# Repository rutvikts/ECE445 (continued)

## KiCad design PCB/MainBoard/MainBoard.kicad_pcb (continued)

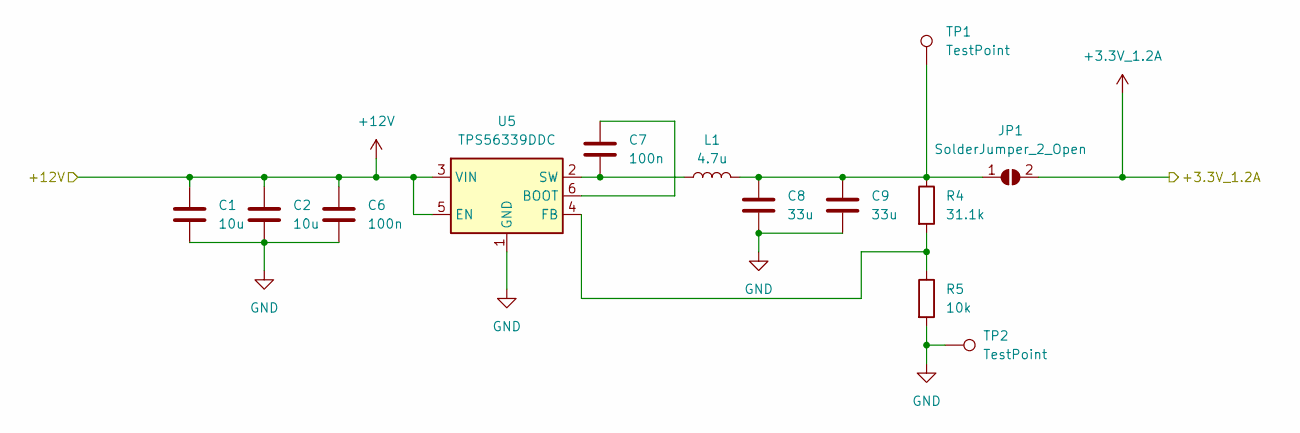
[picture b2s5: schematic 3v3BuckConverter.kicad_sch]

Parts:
C1, C2: 10u; C_1206_3216Metric_Pad1.33x1.80mm_HandSolder
C6, C7: 100n; C_1206_3216Metric_Pad1.33x1.80mm_HandSolder
C8, C9: 33u; C_1206_3216Metric_Pad1.33x1.80mm_HandSolder
JP1: SolderJumper_2_Open; SolderJumper-2_P1.3mm_Open_TrianglePad1.0x1.5mm
L1: 4.7u; L_1008_2520Metric
R4: 31.1k; R_Axial_DIN0207_L6.3mm_D2.5mm_P7.62mm_Horizontal
R5: 10k; R_Axial_DIN0207_L6.3mm_D2.5mm_P7.62mm_Horizontal
TP1, TP2: TestPoint; PinHeader_1x01_P2.54mm_Vertical
U5: TPS56339DDC; SOT-23-6

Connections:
+3.3V_1.2A: JP1.2 (B); also elsewhere on the board
+12V: C1.1, C2.1, C6.1, U5.3 (VIN), U5.5 (EN); also elsewhere on the board
GND: C1.2, C2.2, C6.2, C8.2, C9.2, R5.2, TP2.1, U5.1 (GND); also elsewhere on the board
unnamed: C8.1, C9.1, JP1.1 (A), L1.2, R4.1, TP1.1
unnamed: C7.1, U5.6 (BOOT)
unnamed: R4.2, R5.1, U5.4 (FB)
unnamed: C7.2, L1.1, U5.2 (SW)

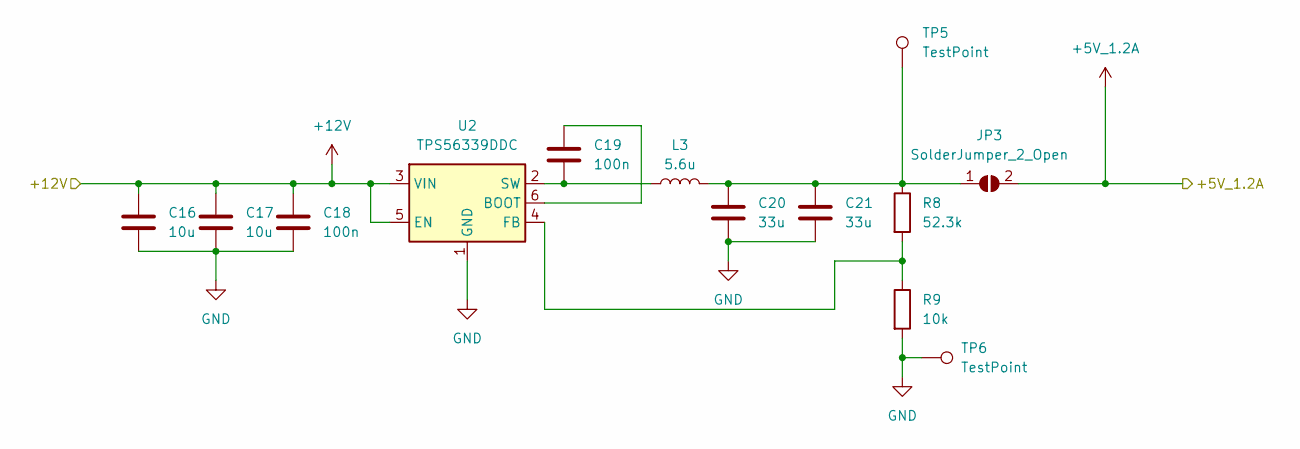
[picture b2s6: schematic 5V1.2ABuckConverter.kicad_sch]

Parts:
C16, C17: 10u; C_1206_3216Metric_Pad1.33x1.80mm_HandSolder
C18, C19: 100n; C_1206_3216Metric_Pad1.33x1.80mm_HandSolder
C20, C21: 33u; C_1206_3216Metric_Pad1.33x1.80mm_HandSolder
JP3: SolderJumper_2_Open; SolderJumper-2_P1.3mm_Open_TrianglePad1.0x1.5mm
L3: 5.6u; L_1008_2520Metric
R8: 52.3k; R_Axial_DIN0207_L6.3mm_D2.5mm_P7.62mm_Horizontal
R9: 10k; R_Axial_DIN0207_L6.3mm_D2.5mm_P7.62mm_Horizontal
TP5, TP6: TestPoint; PinHeader_1x01_P2.54mm_Vertical
U2: TPS56339DDC; SOT-23-6

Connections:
+5V_1.2A: JP3.2 (B); also elsewhere on the board
+12V: C16.1, C17.1, C18.1, U2.3 (VIN), U2.5 (EN); also elsewhere on the board
GND: C16.2, C17.2, C18.2, C20.2, C21.2, R9.2, TP6.1, U2.1 (GND); also elsewhere on the board
unnamed: C20.1, C21.1, JP3.1 (A), L3.2, R8.1, TP5.1
unnamed: C19.1, U2.6 (BOOT)
unnamed: R8.2, R9.1, U2.4 (FB)
unnamed: C19.2, L3.1, U2.2 (SW)

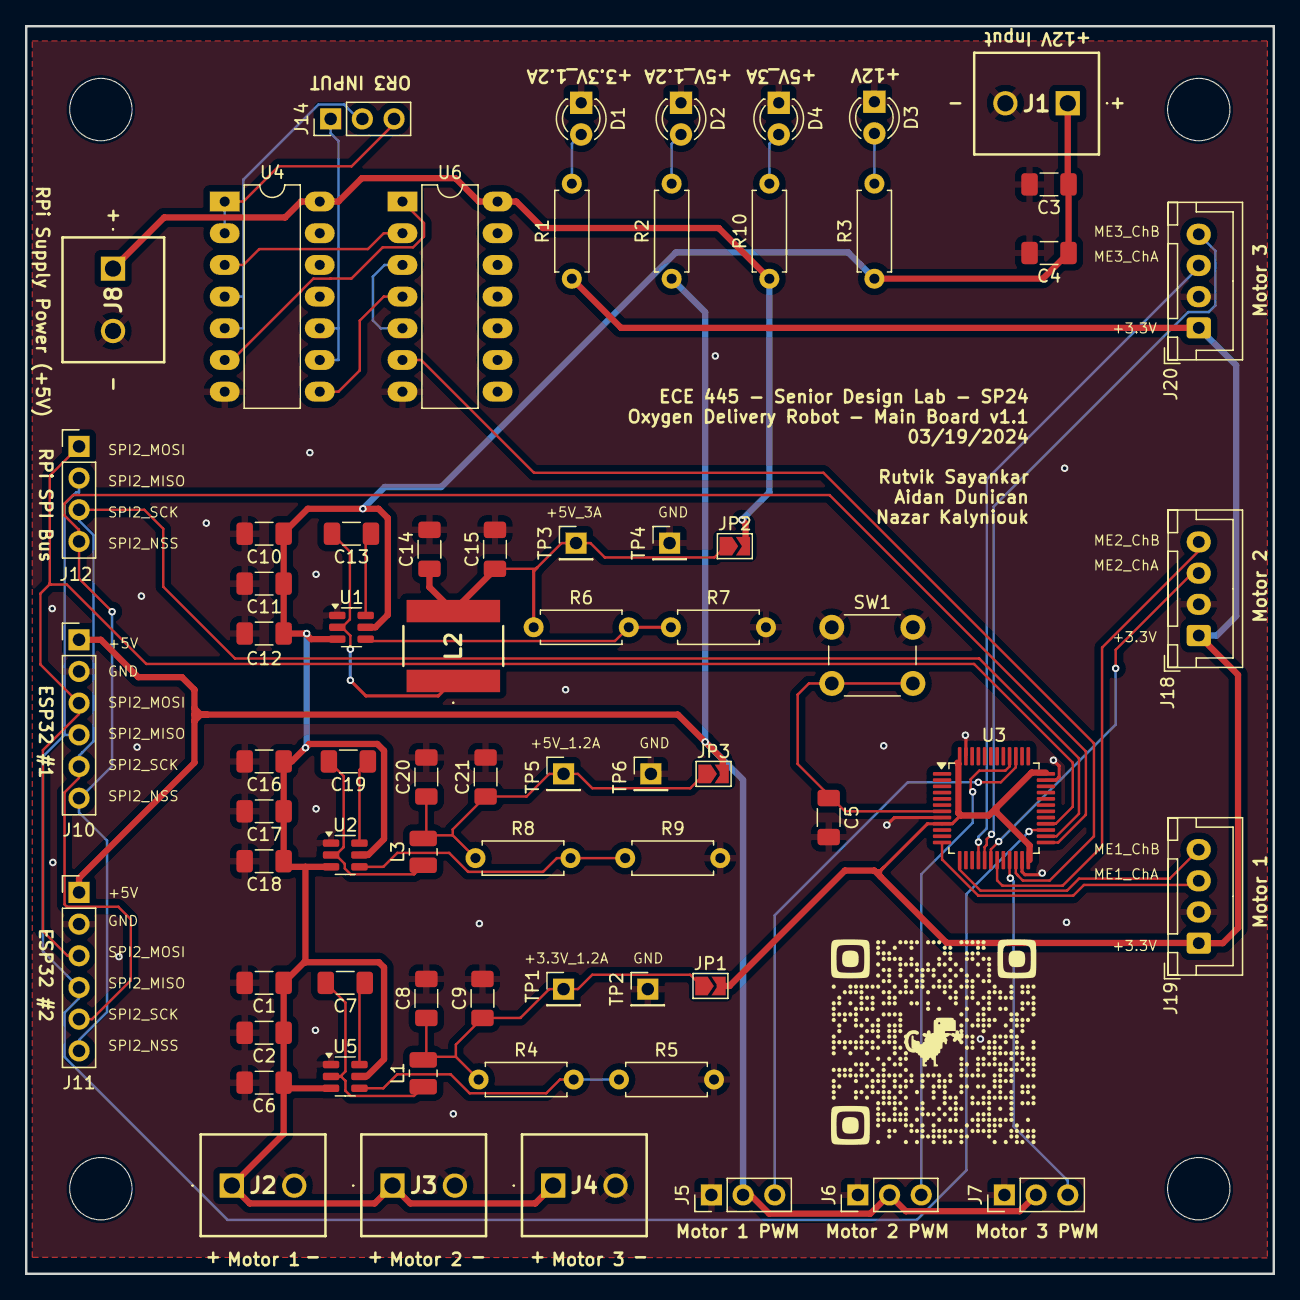
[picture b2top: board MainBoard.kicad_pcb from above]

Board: 2 copper layers, 100.0 x 100.0 mm, 73 parts (0 on the bottom side), 43 nets.

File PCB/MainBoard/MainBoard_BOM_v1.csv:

"Reference","Value","Datasheet","Footprint","Qty","DNP"
"C1,C2,C10,C11,C16,C17","10u","~","Capacitor_SMD:C_1206_3216Metric_Pad1.33x1.80mm_HandSolder","6",""
"C3,C4,C5","0.1uF","~","Capacitor_SMD:C_1206_3216Metric_Pad1.33x1.80mm_HandSolder","3",""
"C6,C7,C12,C13,C18,C19","100n","~","Capacitor_SMD:C_1206_3216Metric_Pad1.33x1.80mm_HandSolder","6",""
"C8,C9,C14,C15,C20,C21","33u","~","Capacitor_SMD:C_1206_3216Metric_Pad1.33x1.80mm_HandSolder","6",""
"D1,D2,D3,D4","LED","~","LED_THT:LED_D3.0mm_Clear","4",""
"H1,H2,H3,H4","MountingHole","~","MountingHole:MountingHole_5mm","4",""
"J4,J8,J9,J17,J21","Conn_01x02_Socket","~","Connector_Wire:SolderWire-0.5sqmm_1x02_P4.8mm_D0.9mm_OD2.3mm","5",""
"J5,J6,J7,J14","Conn_01x03_Socket","~","Connector_PinHeader_2.54mm:PinHeader_1x03_P2.54mm_Vertical","4",""
"J10,J11","Conn_01x06_Socket","~","Connector_PinHeader_2.54mm:PinHeader_1x06_P2.54mm_Vertical","2",""
"J12,J18,J19,J20","Conn_01x04_Socket","~","-- mixed values --","4",""
"JP1,JP2,JP3","SolderJumper_2_Open","~","Jumper:SolderJumper-2_P1.3mm_Open_TrianglePad1.0x1.5mm","3",""
"L1","4.7u","~","Inductor_SMD:L_1008_2520Metric","1",""
"L2","6.8u","~","Inductor_SMD:L_1008_2520Metric","1",""
"L3","5.6u","~","Inductor_SMD:L_1008_2520Metric","1",""
"R1,R2,R3,R10","4.7k","~","Resistor_THT:R_Axial_DIN0207_L6.3mm_D2.5mm_P7.62mm_Horizontal","4",""
"R4","31.1k","~","Resistor_THT:R_Axial_DIN0207_L6.3mm_D2.5mm_P7.62mm_Horizontal","1",""
"R5,R7,R9","10k","~","Resistor_THT:R_Axial_DIN0207_L6.3mm_D2.5mm_P7.62mm_Horizontal","3",""
"R6","53.6k","~","Resistor_THT:R_Axial_DIN0207_L6.3mm_D2.5mm_P7.62mm_Horizontal","1",""
"R8","52.3k","~","Resistor_THT:R_Axial_DIN0207_L6.3mm_D2.5mm_P7.62mm_Horizontal","1",""
"SW1","SW_Push","~","Button_Switch_THT:SW_PUSH_6mm_H7.3mm","1",""
"TP1,TP2,TP3,TP4,TP5,TP6","TestPoint","~","Connector_PinHeader_2.54mm:PinHeader_1x01_P2.54mm_Vertical","6",""
"U1,U2,U5","TPS56339DDC","https://www.ti.com/lit/ds/symlink/tps56339.pdf","Package_TO_SOT_SMD:SOT-23-6","3",""
"U3","STM32F103C8Tx","https://www.st.com/resource/en/datasheet/stm32f103c8.pdf","Package_QFP:LQFP-48_7x7mm_P0.5mm","1",""
"U4,U6","CD74HC00_N_14","","Package_DIP:DIP-14_W7.62mm_LongPads","2",""

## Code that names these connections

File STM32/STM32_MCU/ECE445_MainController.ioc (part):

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Mcu.Name=STM32F103C(8-B)Tx
Mcu.Package=LQFP48
Mcu.UserName=STM32F103C8Tx
PA0-WKUP.GPIOParameters=GPIO_Label
PA0-WKUP.GPIO_Label=TIM2_CH1_ME1_ChA
PA0-WKUP.Signal=S_TIM2_CH1_ETR
PA1.GPIOParameters=GPIO_Label
PA1.GPIO_Label=TIM2_CH2_ME1_ChB
PA1.Signal=S_TIM2_CH2
PA10.GPIOParameters=GPIO_Label
PA10.GPIO_Label=TIM1_CH3\: PWM Motor 3
PA10.Signal=S_TIM1_CH3
PA11.Mode=Device
PA11.Signal=USB_DM
PA12.Mode=Device
PA12.Signal=USB_DP
PA13.Mode=Serial_Wire
PA13.Signal=SYS_JTMS-SWDIO
PA14.Mode=Serial_Wire
PA14.Signal=SYS_JTCK-SWCLK
PA2.GPIOParameters=GPIO_Speed,GPIO_PuPd,GPIO_Label
PA2.GPIO_Label=SPI1_NSS_RasPi
PA2.GPIO_PuPd=GPIO_PULLUP
PA2.GPIO_Speed=GPIO_SPEED_FREQ_HIGH
PA2.Signal=GPIO_Output
PA3.GPIOParameters=GPIO_Speed,GPIO_PuPd,GPIO_Label
PA3.GPIO_Label=SPI1_NSS_ESP2
PA3.GPIO_PuPd=GPIO_PULLUP
PA3.GPIO_Speed=GPIO_SPEED_FREQ_HIGH
PA3.Signal=GPIO_Output
PA4.GPIOParameters=GPIO_Speed,GPIO_PuPd,GPIO_Label
PA4.GPIO_Label=SPI1_NSS_ESP1
PA4.GPIO_PuPd=GPIO_PULLUP
PA4.GPIO_Speed=GPIO_SPEED_FREQ_HIGH
PA4.Signal=GPIO_Output
PA5.Mode=Full_Duplex_Master
PA5.Signal=SPI1_SCK
PA6.Mode=Full_Duplex_Master
PA6.Signal=SPI1_MISO
PA7.Mode=Full_Duplex_Master
PA7.Signal=SPI1_MOSI
PA8.GPIOParameters=GPIO_Label
PA8.GPIO_Label=TIM1_CH1\: PWM Motor 1
PA8.Signal=S_TIM1_CH1
PA9.GPIOParameters=GPIO_Label
PA9.GPIO_Label=TIM1_CH2\: PWM Motor 2
PA9.Signal=S_TIM1_CH2
PB4.GPIOParameters=GPIO_Label
PB4.GPIO_Label=TIM3_CH1_ME2_ChA
PB4.Signal=S_TIM3_CH1
PB5.GPIOParameters=GPIO_Label
PB5.GPIO_Label=TIM3_CH2_ME2_ChB
PB5.Signal=S_TIM3_CH2
PB6.GPIOParameters=GPIO_Label
PB6.GPIO_Label=TIM4_CH1_ME3_ChA
PB6.Signal=S_TIM4_CH1
PB7.GPIOParameters=GPIO_Label
PB7.GPIO_Label=TIM4_CH2_ME3_ChB
PB7.Signal=S_TIM4_CH2
PB9.GPIOParameters=GPIO_PuPd,GPIO_Label
PB9.GPIO_Label=OR3_LimitSwitches
PB9.GPIO_PuPd=GPIO_PULLDOWN
PB9.Signal=GPIO_Input
PD0-OSC_IN.Mode=HSE-External-Oscillator
PD0-OSC_IN.Signal=RCC_OSC_IN
PD1-OSC_OUT.Mode=HSE-External-Oscillator
PD1-OSC_OUT.Signal=RCC_OSC_OUT
RCC.SYSCLKFreq_VALUE=48000000
RCC.SYSCLKSource=RCC_SYSCLKSOURCE_PLLCLK
board=custom

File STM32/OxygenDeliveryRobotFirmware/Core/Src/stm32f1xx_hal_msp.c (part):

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
    __HAL_RCC_GPIOA_CLK_ENABLE();
    /**SPI1 GPIO Configuration
    PA5     ------> SPI1_SCK
    PA6     ------> SPI1_MISO
    PA7     ------> SPI1_MOSI
    */
    GPIO_InitStruct.Pin = GPIO_PIN_5|GPIO_PIN_7;
    GPIO_InitStruct.Mode = GPIO_MODE_AF_PP;
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    __HAL_RCC_SPI1_CLK_DISABLE();

    /**SPI1 GPIO Configuration
    PA5     ------> SPI1_SCK
    PA6     ------> SPI1_MISO
    PA7     ------> SPI1_MOSI
    */
    HAL_GPIO_DeInit(GPIOA, GPIO_PIN_5|GPIO_PIN_6|GPIO_PIN_7);

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
    __HAL_RCC_GPIOA_CLK_ENABLE();
    /**TIM2 GPIO Configuration
    PA0-WKUP     ------> TIM2_CH1
    PA1     ------> TIM2_CH2
    */
    GPIO_InitStruct.Pin = TIM2_CH1_ME1_ChA_Pin|TIM2_CH2_ME1_ChB_Pin;
    GPIO_InitStruct.Mode = GPIO_MODE_INPUT;
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
    __HAL_RCC_GPIOB_CLK_ENABLE();
    /**TIM3 GPIO Configuration
    PB4     ------> TIM3_CH1
    PB5     ------> TIM3_CH2
    */
    GPIO_InitStruct.Pin = TIM3_CH1_ME2_ChA_Pin|TIM3_CH2_ME2_ChB_Pin;
    GPIO_InitStruct.Mode = GPIO_MODE_INPUT;
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
    __HAL_RCC_GPIOB_CLK_ENABLE();
    /**TIM4 GPIO Configuration
    PB6     ------> TIM4_CH1
    PB7     ------> TIM4_CH2
    */
    GPIO_InitStruct.Pin = TIM4_CH1_ME3_ChA_Pin|TIM4_CH2_ME3_ChB_Pin;
    GPIO_InitStruct.Mode = GPIO_MODE_INPUT;
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
    __HAL_RCC_GPIOA_CLK_ENABLE();
    /**TIM1 GPIO Configuration
    PA8     ------> TIM1_CH1
    PA9     ------> TIM1_CH2
    PA10     ------> TIM1_CH3
    */
    GPIO_InitStruct.Pin = TIM1_CH1__PWM_Motor_1_Pin|TIM1_CH2__PWM_Motor_2_Pin|TIM1_CH3__PWM_Motor_3_Pin;
    GPIO_InitStruct.Mode = GPIO_MODE_AF_PP;
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    __HAL_RCC_TIM2_CLK_DISABLE();

    /**TIM2 GPIO Configuration
    PA0-WKUP     ------> TIM2_CH1
    PA1     ------> TIM2_CH2
    */
    HAL_GPIO_DeInit(GPIOA, TIM2_CH1_ME1_ChA_Pin|TIM2_CH2_ME1_ChB_Pin);

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    __HAL_RCC_TIM3_CLK_DISABLE();

    /**TIM3 GPIO Configuration
    PB4     ------> TIM3_CH1
    PB5     ------> TIM3_CH2
    */
    HAL_GPIO_DeInit(GPIOB, TIM3_CH1_ME2_ChA_Pin|TIM3_CH2_ME2_ChB_Pin);

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    __HAL_RCC_TIM4_CLK_DISABLE();

    /**TIM4 GPIO Configuration
    PB6     ------> TIM4_CH1
    PB7     ------> TIM4_CH2
    */
    HAL_GPIO_DeInit(GPIOB, TIM4_CH1_ME3_ChA_Pin|TIM4_CH2_ME3_ChB_Pin);

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
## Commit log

2024-02-04 uploading initial research progress
2024-02-04 Update .gitignore for DS_Store files
2024-02-04 updated readme & created project proposal file
2024-02-06 Uploading block diagram
2024-02-06 adding DS_Store ignore note in gitignore
2024-02-08 Adding txt files for TA check-ins
2024-02-08 Updated Team Contract
2024-02-09 uploading team contract file
2024-02-09 adding new project proposal
2024-02-18 Create Motor Research - Sheet1.pdf
    Motor Research
2024-02-19 Update AidanProgress.txt
    Started drivetrain portion of pcb research
2024-02-20 Motor Research Update
2024-02-22 updating progress file
2024-02-22 Project Proposal Revisions
2024-02-29 updated .gitignore for .lck files in KiCAD
2024-02-29 Adding PCB progress with Power subsection and adding STM32
2024-02-29 updating progress section
2024-02-29 adding some misc images and files
2024-03-01 updating pcb
2024-03-01 updating progress
2024-03-04 5v 1.2A buck converter
2024-03-04 3.3v .15A buck converter
2024-03-04 adding nazar's work onto new branch
2024-03-04 updating power schematics, and power lines
2024-03-05 passed ERC in schematic
2024-03-05 began placing components - motor connectors, 12V in, mounting holes
2024-03-05 Placed Buck Converters and changed inductors to 1008
2024-03-05 updated pcb schematic
2024-03-05 final layout v1 - unconnected
2024-03-05 board routed, just need to increase track widths for power lines
2024-03-05 Updated PCB and passed DRC
2024-03-05 Created Gerber Files
2024-03-18 Exported BOM
2024-03-18 Updating main PCB for version 1.1
2024-03-18 updating v1.1 with chamfered traces
2024-03-19 updating PCB with new components and proper footprints, still need to fix footprint matching issue.
2024-03-19 fixing some right angles in board
2024-03-19 v1.1 of MainBoard complete - PCBWay DRC Passes
2024-03-19 organizing Rutvik progress section
2024-03-20 Updated Design Doc Latex code
2024-03-20 Updated Design Doc
2024-03-21 updating latex document
2024-03-21 adding latex environment files plus updated design doc
2024-03-22 Adding Manufacturer OWB Test Code
2024-03-25 Updated AidanProgress.txt
2024-03-26 updating 3d printing files and progress report - rutvik
2024-03-26 updating rutvik's progress report
2024-03-28 adding 3d printing stl files for limit switch bumper
2024-03-28 updating IPR progress
2024-04-01 Updated progress and uploaded bumper cad file
2024-04-01 pushing 3d printing stl files
2024-04-02 starting stm32cube pin mapping
2024-04-02 adding all stm32 projects
2024-04-03 adding board v2 progress
2024-04-04 Updating progress on board v2
2024-04-05 updating main board v2 progress
2024-04-05 updating main board v2 with motor power conns
2024-04-05 updating progress for board v2
2024-04-05 board v2 passing ERC in schematic
2024-04-05 footprints all assigned for board v2
2024-04-07 Updated part assignments on board for digikey order
2024-04-07 pushing progress on mainboard v2 layout
2024-04-08 Main Board v2 Rough component layout complete
2024-04-09 updating layout progress, adding limit switch extra circuitry
2024-04-09 PCB laid out & passes DRC
2024-04-09 main board v2 sent to fab
2024-04-15 pushing final report setup
2024-04-15 Started work on limit switch stm code
2024-04-17 UWB files update
2024-04-18 pushing stm stuff
2024-04-18 MainBoard STM Code
2024-04-19 adding stm progress and contract fulfillment
2024-04-19 stm spi setup
2024-04-19 repo clean up, orgainizing stm32 folders, deleting mainbaordv2.1
    deleting mainbaordv2.1 as it was never completed. too many misc stm32 folders, consolidated for orgaization
2024-04-20 adding 3d printing files for bumper
2024-04-20 adding new folder for firmware development
2024-04-23 adding limit switch update and oxygen tank standoff
2024-04-23 updating standoff
2024-04-23 updating firmware for delivery robot, scaling motor speed with map
2024-04-23 working serial debugging through USB
2024-04-23 misc files for STM32 old directory
2024-04-23 created final block diagram
2024-04-23 all encoders working
2024-04-23 updating firmware software tuning
2024-04-24 adding battery housing 3d print file
2024-04-25 Code push before Demo!
2024-04-26 Pushed Demo Code
2024-04-26 adding printout files
2024-04-28 updating final report latex
2024-04-28 updating latex final report
2024-04-28 updating latex
2024-04-29 adding battery housing creality file
2024-04-29 getting presentation screenshots, nothing changed
2024-05-02 Pushing final report files
2024-05-02 adding final robot pics and repo organization
2024-05-02 Update README.md for project pic
2024-05-02 Update README.md testing image showing on github
2024-05-02 Distance and Angle calculations
2024-05-02 OpenCV Verification (Image, Video, Demo)
2024-05-02 updating robot pics
2024-05-02 Update README.md with proper images
